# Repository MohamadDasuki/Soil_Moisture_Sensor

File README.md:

# Soil Moisture Sensor

Button-activated, battery-powered soil moisture meter with a 0.96" OLED display.

Press the button -> MCU wakes -> load switch powers the OLED and sensor -> moisture reading is shown for 15 s -> everything powers down (<1 uA standby).

## Hardware
| Ref | Function | Part |
|---|---|---|
| U1 | MCU | Microchip ATtiny1614-SSNR (SOIC-14) |
| J5 | Battery | 3xAAA holder, leads soldered to J5 pads (+ = pin 1; direct, 3.0-4.8 V) |
| Q1 | Reverse-polarity protection | AOS AO3401A P-FET |
| U2 | Peripheral power switch | TI TPS22917DBVR load switch |
| J2 | Display | ELEGOO 0.96" SSD1306 I2C OLED (0x3C) - 2.54 mm pads, GND-VCC-SCL-SDA |
| J3 | Sensor | DIYmall capacitive soil sensor v1.2 (analog) - 2.54 mm pads, GND-VCC-AOUT |
| SW1 | Button | Twidec PBS-110 7 mm panel-mount momentary, leads soldered to 2 pads |
| J1 | Programming | UPDI through-hole pads on the board edge (UPDI-GND-VCC) |

See `BOM.csv` for the full parts list and `Moisture_Sensor.pdf` for the schematic.

## PCB (rev C)
- 24 x 19 mm, 2-layer, 1.6 mm, all SMD on top, GND pour both sides.
- Top edge: OLED (G V C D) and sensor (G V A) pads. Bottom edge: UPDI (U G V) and button pads.
- Solder the supplied Dupont/PH cables directly to the pads (or fit 2.54 mm headers).
- No mounting holes: hold the board with a ledge/snap clips. `Moisture_Sensor.step` is provided for enclosure design.

## Programming
UPDI via a 3.3 V USB-serial adapter with a 4.7k resistor TX->UPDI, RX->UPDI ("SerialUPDI"), or an Adafruit UPDI Friend.
Arduino IDE + megaTinyCore, board ATtiny1614, programmer SerialUPDI. Remove batteries when powering from the programmer.

## Pin map (ATtiny1614)
| Signal | Port | Pin |
|---|---|---|
| LOAD_EN | PA4 | 2 |
| AOUT (sensor, ADC) | PA5 | 3 |
| BTN (wake) | PA6 | 4 |
| SDA | PB1 | 8 |
| SCL | PB0 | 9 |
| UPDI | PA0 | 10 |

## Firmware

`firmware/MoistureMeter/` contains an Arduino sketch for megaTinyCore. It uses 4.7 KB of flash and 75 B of RAM, and needs no external libraries. The SSD1306 driver in `oled.h` is buffer-less (text only).

**Operation**
- **Idle:** the MCU is in power-down and the load switch is off (well under 1 µA).
- **Press the button:** the OLED and sensor power up and the battery voltage is checked. The display then shows a live moisture % reading, refreshed every second, with a status line (DRY / OK / WET) and a bar graph. After 15 s it powers everything off.
- **Short press while on:** restarts the 15 s timer.
- **Hold 3 s while on:** starts calibration. Follow the prompts: sensor in air, press; sensor in water up to the line, press. The values are saved to EEPROM.
- **Battery below 3.1 V:** shows "BATTERY EMPTY" instead of a reading. Below 3.4 V, the header shows "LOW BAT".
- **Battery voltage:** measured by reading the internal 1.1 V reference against VDD, so no divider is needed. The sensor is read ratiometrically (ADC reference = VDD), so battery droop cancels out.

**Build and flash**
- Arduino IDE: add the board manager URL `http://drazzy.com/package_drazzy.com_index.json` and install **megaTinyCore**.
- Tools settings: Chip **ATtiny1614**, Clock **5 MHz internal**, BOD **Disabled/Disabled**, millis timer **default (not RTC)**, Programmer **SerialUPDI**.
- Run **Burn Bootloader** once (this only sets fuses), then **Upload Using Programmer**.
- With arduino-cli, use the FQBN `megaTinyCore:megaavr:atxy4:chip=1614,clock=5internal,bodmode=disabled`.

Calibration defaults are typical v1.2 values (dry ≈ 600/1023, wet ≈ 280/1023). Calibrate once per sensor for accurate readings.
## Ordering (JLCPCB)

The `fab/` folder holds everything needed to order the board:

| File | Upload as |
|---|---|
| `Moisture_Sensor_gerbers_JLCPCB.zip` | Gerber file (2 layers, 24 × 19 mm, 1.6 mm FR-4) |
| `BOM_JLCPCB.csv` | PCB Assembly → BOM (LCSC part numbers) |
| `CPL_JLCPCB.csv` | PCB Assembly → CPL (pick and place) |

- **Assembly:** top side only, SMD parts only. J1, J2, J3, J5 and SW1 are hand-soldered wire pads and aren't placed.
- **Before confirming,** check pin 1 of U1, U2 and Q1 in JLCPCB's placement preview. The CPL applies the usual rotation offsets for SOT-23 and SOIC parts.
- **Regenerating:**
  - CPL and JLCPCB BOM: run `tools/gen_cpl.py` with KiCad's Python.
  - Gerbers and drill files: export with `kicad-cli pcb export gerbers` (subtract soldermask, no X2) and `kicad-cli pcb export drill` (Excellon, mm, separate PTH/NPTH).
## Enclosure

| | |
|---|---|
|  |  |
|  |  |

Outer size **42 × 111 × 18.4 mm**. Generated by `tools/gen_enclosure.py`, which is fully parametric (run it with FreeCAD's `freecadcmd.exe`). The script also checks for interference against the real PCB STEP model and against dummy models of the OLED, the AAA cells and the button. `tools/render_enclosure.py` (run with `freecad.exe`) regenerates the images.

| Part | File | Print orientation |
|---|---|---|
| Body (tub) | `enclosure/body.stl` | display face down, as exported |
| Lid | `enclosure/lid.stl` | outer face down, as exported |
| Battery door | `enclosure/door.stl` | outer face down, as exported |

**Printing:** no supports are needed. The button hole is a teardrop, the display window has a 45° chamfer, the clip lips overhang by 0.5 mm or less, and the door rails are 45° dovetails. Use 0.2 mm layers, 3–4 perimeters, and **PETG** (recommended for the snap clips). PLA works, but the clips run at about 3 % strain.

**Features**
- **Display:** a window in the front face. The module drops into a pocket with corner ledges, and the lid has 4 posts that clamp the module's corners.
- **PCB:** held by 3 flexible snap clips plus 1 rigid hook, on 3 mm standoffs. To insert it, tilt the board and slide its J2/J3 edge (toward the display) under the rigid hook, then press the other edge down until the clips snap.
- **Button:** a 7 mm hole in the top end wall. The nut tightens from inside.
- **Sensor cable:** a U-notch in the side wall at the lid seam, so the cable is laid in rather than threaded. Weave the cable around the 3 posts for strain relief.
- **Batteries:** 3×AAA side by side behind a sliding dovetail door. To open it, lift the flex tab at the finger grooves and slide the door out toward the bottom end.
  - Contacts are generic AAA plates/springs in 0.8 mm slots: a single plate for 10 mm-wide contacts, a double slot for 21 mm-wide bridging contacts.
  - Top fence: single (+, cell 1, left) and double (cells 2/3).
  - Bottom fence: double (cells 1/2) and single (−, cell 3).
  - Solder the + and − wires to the J5 pads (B+ / B− on the back silkscreen).
- **Lid:** snap-fit with 4 tabs; no screws. Open it only for programming (the UPDI pads are reachable with the lid off).

**Verify before printing** (all are parameters at the top of `gen_enclosure.py`):
- OLED glass and viewing-area offsets (`GLASS_*`, `VIEW_*`).
- Button body length (the space behind the wall is about 18 mm).
- Contact plate dimensions.
- Rebuild after any change.
## Notes
- Sensor: bypass its onboard 662K LDO (the NE555 is otherwise starved at 3.3 V). Its output then scales with supply, so read it ratiometrically (ADC reference = VDD). Calibrate dry/wet values in firmware.
- OLED runs from VSW through its own LDO (3.3-5 V); no mod needed.
- Firmware: 10 MHz is fine (>2.7 V); set I2C pins high-Z before switching off VSW; low-battery cutoff ~3.3 V.
- `tools/gen_sch.py` regenerates the schematic and `tools/gen_pcb.py --route` the PCB (KiCad's bundled Python; routing needs Freerouting + Java 25).

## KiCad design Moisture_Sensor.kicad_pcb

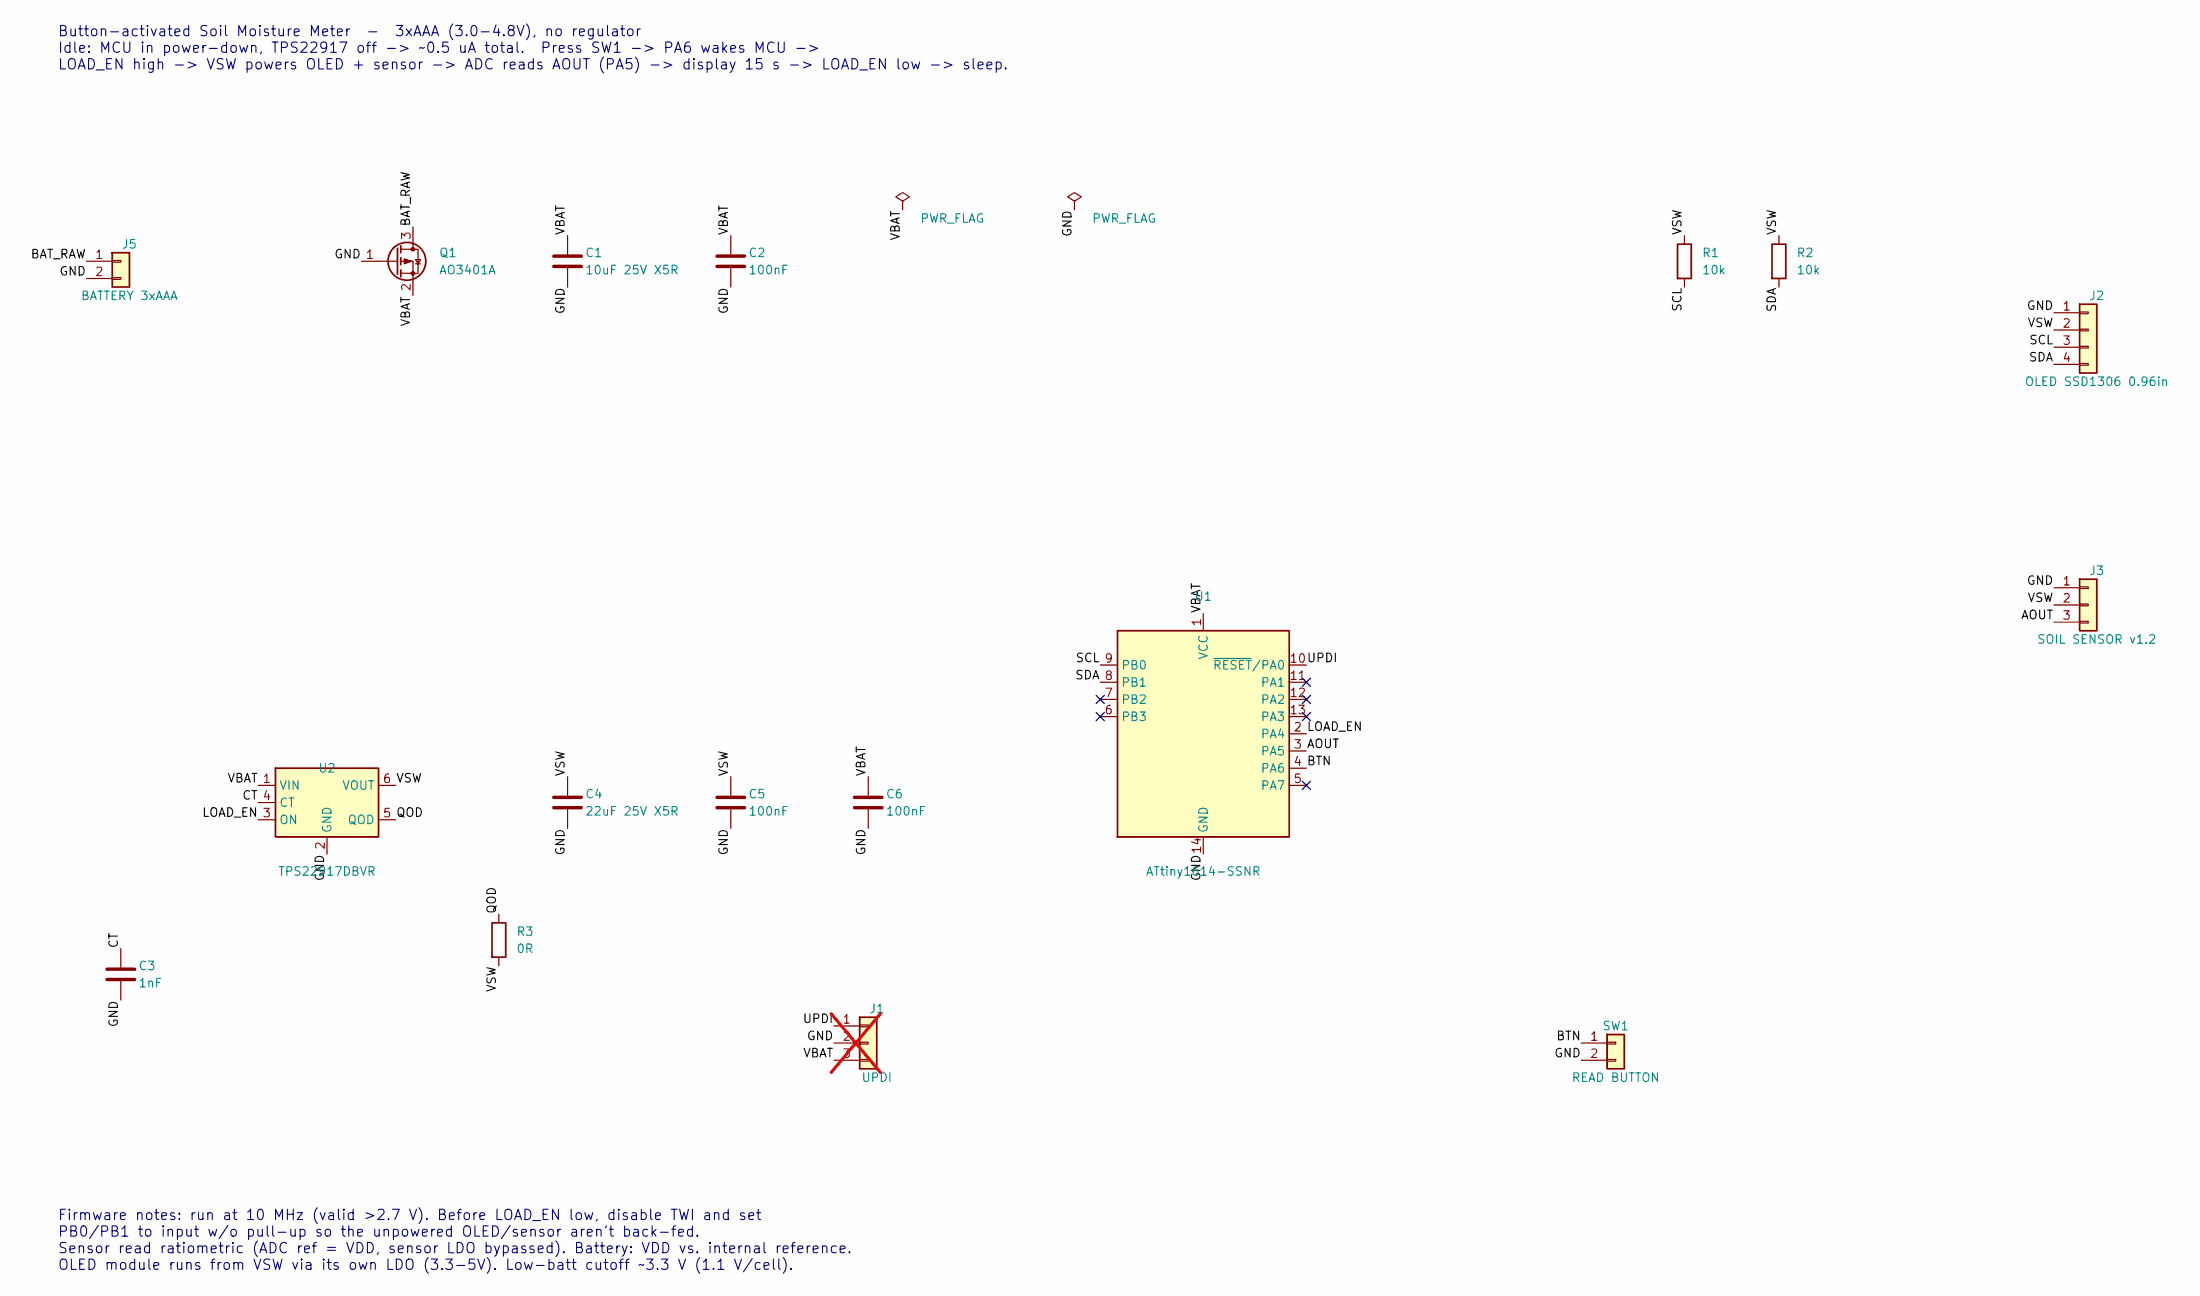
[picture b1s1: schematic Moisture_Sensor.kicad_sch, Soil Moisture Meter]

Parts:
C1: 10uF 25V X5R; C_0805_2012Metric; MPN CL21A106KAYNNNE; LCSC C15850
C2, C5, C6: 100nF; C_0603_1608Metric; MPN CC0603KRX7R9BB104; LCSC C14663
C3: 1nF; C_0603_1608Metric; MPN CL10B102KB8NNNC; LCSC C1588
C4: 22uF 25V X5R; C_0805_2012Metric; MPN CL21A226MAQNNNE; LCSC C45783
J1: UPDI; PinHeader_1x03_P2.54mm_Vertical; not fitted
J2: OLED SSD1306 0.96in; PinHeader_1x04_P2.54mm_Vertical; MPN Supplied Dupont wires soldered to pads 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
J3: SOIL SENSOR v1.2; PinHeader_1x03_P2.54mm_Vertical; MPN Supplied PH2.0-3P to Dupont cable solde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
J5: BATTERY 3xAAA; PinHeader_1x02_P2.54mm_Vertical; MPN 3xAAA holder leads soldered to pads
Q1: AO3401A; SOT-23; MPN AO3401A; LCSC C15127
R1, R2: 10k; R_0603_1608Metric; MPN 0603WAF1002T5E; LCSC C25804
R3: 0R; R_0603_1608Metric; MPN 0603WAF0000T5E; LCSC C21189
SW1: READ BUTTON; PinHeader_1x02_P2.54mm_Vertical; MPN PBS-110-XBK
U1: ATtiny1614-SSNR; SOIC-14_3.9x8.7mm_P1.27mm; MPN ATTINY1614-SSNR; LCSC C481364
U2: TPS22917DBVR; SOT-23-6; MPN TPS22917DBVR; LCSC C2681320

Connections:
/AOUT: J3.3, U1.3 (PA5)
/BAT_RAW: J5.1, Q1.3 (D)
/BTN: SW1.1, U1.4 (PA6)
/CT: C3.1, U2.4 (CT)
/GND: C1.2, C2.2, C3.2, C4.2, C5.2, C6.2, J1.2, J2.1, J3.1, J5.2, Q1.1 (G), SW1.2, U1.14 (GND), U2.2 (GND)
/LOAD_EN: U1.2 (PA4), U2.3 (ON)
/QOD: R3.1, U2.5 (QOD)
/SCL: J2.3, R1.2, U1.9 (PB0)
/SDA: J2.4, R2.2, U1.8 (PB1)
/UPDI: J1.1, U1.10 (~RESET/PA0)
/VBAT: C1.1, C2.1, C6.1, J1.3, Q1.2 (S), U1.1 (VCC), U2.1 (VIN)
/VSW: C4.1, C5.1, J2.2, J3.2, R1.1, R2.1, R3.2, U2.6 (VOUT)

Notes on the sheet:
Button-activated Soil Moisture Meter - 3xAAA (3.0-4.8V), no regulator Idle: MCU in power-down, TPS22917 off -> ~0.5 uA total. Press SW1 -> PA6 wakes MCU -> LOAD_EN high -> VSW powers OLED + sensor -> ADC reads AOUT (PA5) -> display 15 s -> LOAD_EN low -> sleep.
Firmware notes: run at 10 MHz (valid >2.7 V). Before LOAD_EN low, disable TWI and set PB0/PB1 to input w/o pull-up so the unpowered OLED/sensor aren't back-fed. Sensor read ratiometric (ADC ref = VDD, sensor LDO bypassed). Battery: VDD vs. internal reference. OLED module runs from VSW via its own L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

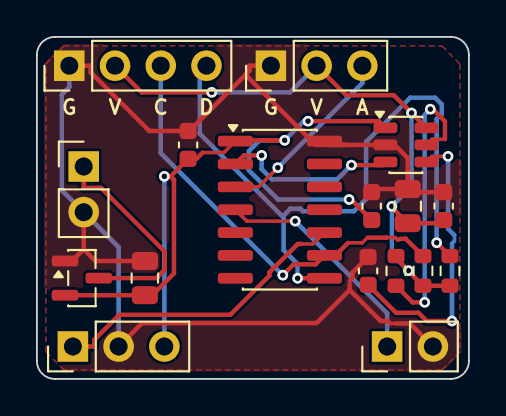
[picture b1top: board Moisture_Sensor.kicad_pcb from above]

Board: 2 copper layers, 24.0 x 19.0 mm, 17 parts (0 on the bottom side), 12 nets.

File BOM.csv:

"Reference","Value","Footprint","MPN","Manufacturer","LCSC","QUANTITY","DNP"
"C1","10uF 25V X5R","Capacitor_SMD:C_0805_2012Metric","CL21A106KAYNNNE","Samsung","C15850","1",""
"C2,C5,C6","100nF","Capacitor_SMD:C_0603_1608Metric","CC0603KRX7R9BB104","Yageo","C14663","3",""
"C3","1nF","Capacitor_SMD:C_0603_1608Metric","CL10B102KB8NNNC","Samsung","C1588","1",""
"C4","22uF 25V X5R","Capacitor_SMD:C_0805_2012Metric","CL21A226MAQNNNE","Samsung","C45783","1",""
"J1","UPDI","Connector_PinHeader_2.54mm:PinHeader_1x03_P2.54mm_Vertical","","","","1","DNP"
"J2","OLED SSD1306 0.96in","Connector_PinHeader_2.54mm:PinHeader_1x04_P2.54mm_Vertical","Supplied Dupont wires soldered to pads (opt. 1x04 2.54mm header)","-","","1",""
"J3","SOIL SENSOR v1.2","Connector_PinHeader_2.54mm:PinHeader_1x03_P2.54mm_Vertical","Supplied PH2.0-3P to Dupont cable soldered to pads","DIYmall","","1",""
"J5","BATTERY 3xAAA","Connector_PinHeader_2.54mm:PinHeader_1x02_P2.54mm_Vertical","3xAAA holder leads soldered to pads","-","","1",""
"Q1","AO3401A","Package_TO_SOT_SMD:SOT-23","AO3401A","Alpha & Omega","C15127","1",""
"R1,R2","10k","Resistor_SMD:R_0603_1608Metric","0603WAF1002T5E","UNI-ROYAL","C25804","2",""
"R3","0R","Resistor_SMD:R_0603_1608Metric","0603WAF0000T5E","UNI-ROYAL","C21189","1",""
"SW1","READ BUTTON","Connector_PinHeader_2.54mm:PinHeader_1x02_P2.54mm_Vertical","PBS-110-XBK","Twidec","","1",""
"U1","ATtiny1614-SSNR","Package_SO:SOIC-14_3.9x8.7mm_P1.27mm","ATTINY1614-SSNR","Microchip","C481364","1",""
"U2","TPS22917DBVR","Package_TO_SOT_SMD:SOT-23-6","TPS22917DBVR","Texas Instruments","C2681320","1",""

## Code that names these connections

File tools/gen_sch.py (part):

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      "9": "SCL", "8": "SDA",
      "11": None, "12": None, "13": None, "5": None, "6": None, "7": None},
     {"MPN": "ATTINY1614-SSNR", "Manufacturer": "Microchip", "LCSC": "C481364"}, False),
    ("J1", "Connector_Generic", "Conn_01x03", "UPDI", "Connector_PinHeader_2.54mm:PinHeader_1x03_P2.54mm_Vertical",
     150, 175, {"1": "UPDI", "2": "GND", "3": "VBAT"},
     {"Note": "UPDI through-hole pads on board edge; plug Dupont wires / temporary header (3.3V SerialUPDI)"}, True),
    ("SW1", "Connector_Generic", "Conn_01x02", "READ BUTTON", "Connector_PinHeader_2.54mm:PinHeader_1x02_P2.54mm_Vertical",
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         {"MPN": "Supplied Dupont wires soldered to pads (opt. 1x04 2.54mm header)", "Manufacturer": "-", "Note": "ELEGOO 0.96in SSD1306 module, pin order GND-VCC-SCL-SDA"}, False),
    ("J3", "Connector_Generic", "Conn_01x03", "SOIL SENSOR v1.2", "Connector_PinHeader_2.54mm:PinHeader_1x03_P2.54mm_Vertical",
     330, 110, {"1": "GND", "2": "VSW", "3": "AOUT"},
     {"MPN": "Supplied PH2.0-3P to Dupont cable soldered to pads", "Manufacturer": "DIYmall", "Note": "Capacitive soil sensor v1.2, analog 0-3V, GND-VCC-AOUT; bypass its 662K LDO"}, False),
]

notes = [
    (30, 25, "Button-activated Soil Moisture Meter  -  3xAAA (3.0-4.8V), no regulator\n"
             "Idle: MCU in power-down, TPS22917 off -> ~0.5 uA total.  Press SW1 -> PA6 wakes MCU ->\n"
             "LOAD_EN high -> VSW powers OLED + sensor -> ADC reads AOUT (PA5) -> display 15 s -> LOAD_EN low -> sleep."),
    (30, 200, "Firmware notes: run at 10 MHz (valid >2.7 V). Before LOAD_EN low, disable TWI and set\n"
              "PB0/PB1 to input w/o pull-up so the unpowered OLED/sensor aren't back-fed.\n"
              "Sensor read ratiometric (ADC ref = VDD, sensor LDO bypassed). Battery: VDD vs. internal reference.\n"
              "OLED module runs from VSW via its own LDO (3.3-5V). Low-batt cutoff ~3.3 V (1.1 V/cell)."),
]
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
